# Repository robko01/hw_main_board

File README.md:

# hw_main_board
This repo is holding the Robko 01 main board design.

The board is designed in KiCAD.

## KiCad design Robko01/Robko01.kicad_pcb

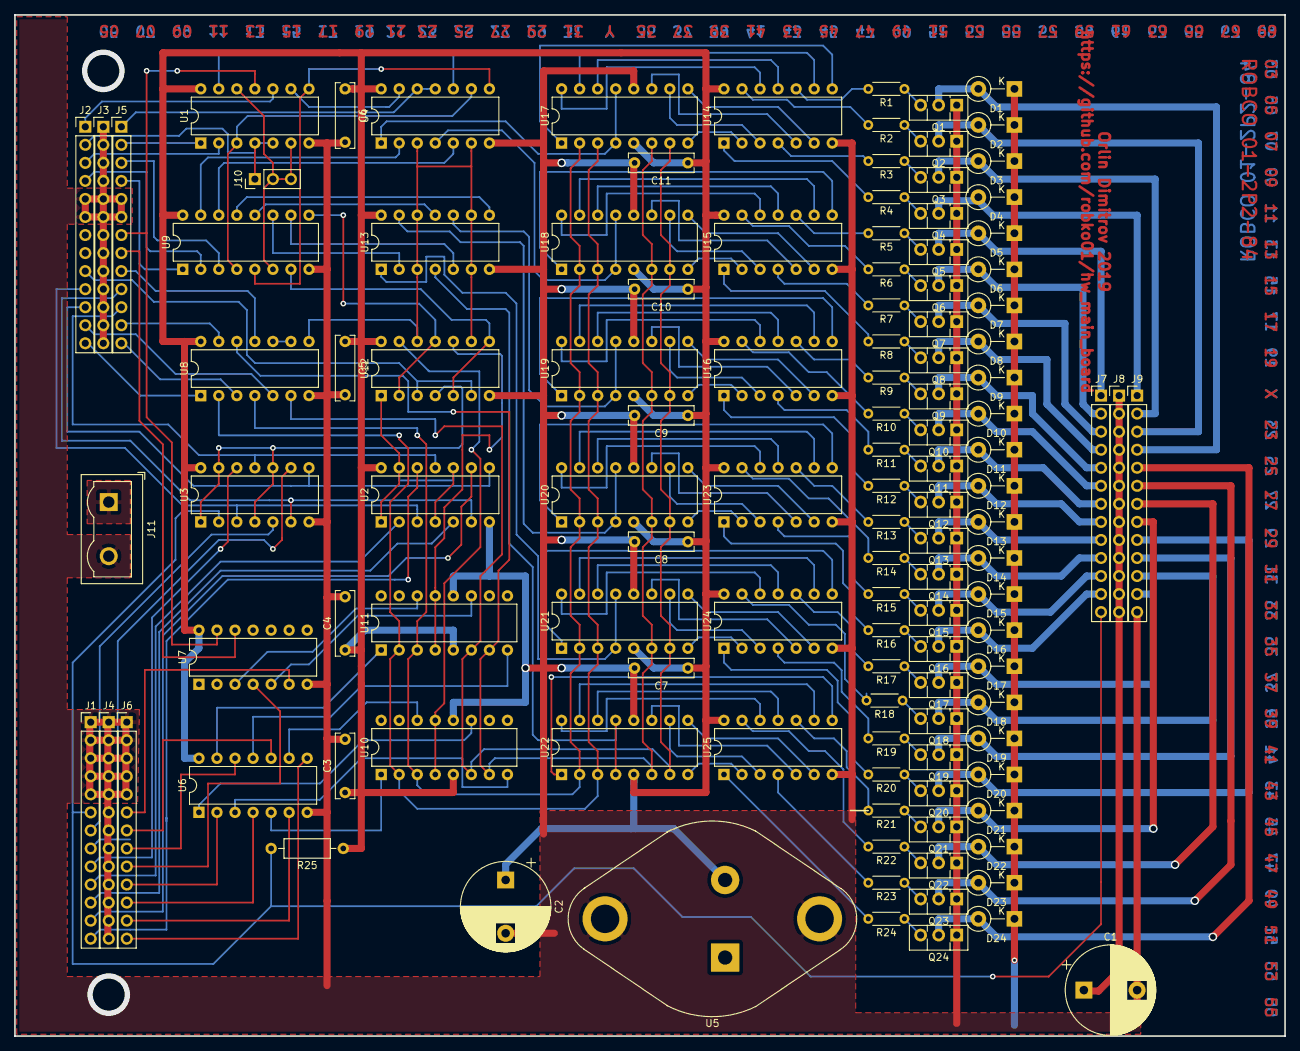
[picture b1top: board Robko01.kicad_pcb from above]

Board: 2 copper layers, 178.8 x 143.8 mm, 120 parts (0 on the bottom side), 196 nets.

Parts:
C1, C2: CP; CP_Radial_D12.5mm_P7.50mm
C3, C4, C5, C6, C7, C8, C9, C10, C11: 150nF; C_Rect_L9.0mm_W2.5mm_P7.50mm_MKT
D1, D2, D3, D4, D5, D6, D7, D8, D9, D10, D11, D12, D13, D14, D15, D16, D17, D18, D19, D20, D21, D22, D23, D24: 1N4007; D_DO-41_SOD81_P5.08mm_Vertical_KathodeUp
J1: AC; PinHeader_1x13_P2.54mm_Vertical
J2, J5: BA; PinHeader_1x13_P2.54mm_Vertical
J3: BB; PinHeader_1x13_P2.54mm_Vertical
J4: AB; PinHeader_1x13_P2.54mm_Vertical
J6: AA; PinHeader_1x13_P2.54mm_Vertical
J7, J8, J9: MA; PinHeader_1x13_P2.54mm_Vertical
J10: A_SEL; PinHeader_1x03_P2.54mm_Vertical
J11: Conn_01x02_Male; TerminalBlock_Wuerth_691311400102_P7.62mm
Q1, Q2, Q3, Q4, Q5, Q6, Q7, Q8, Q9, Q10, Q11, Q12, Q13, Q14, Q15, Q16, Q17, Q18, Q19, Q20, Q21, Q22, Q23, Q24: BD139; TO-126-3_Vertical
R1, R2, R3, R4, R5, R6, R7, R8, R9, R10, R11, R12, R13, R14, R15, R16, R17, R18, R19, R20, R21, R22, R23, R24: R; R_Axial_DIN0204_L3.6mm_D1.6mm_P5.08mm_Horizontal
R25: 10k; R_Axial_DIN0207_L6.3mm_D2.5mm_P10.16mm_Horizontal
U1: 7400; DIP-14_W7.62mm
U2, U3: 74126; DIP-14_W7.62mm
U4, U12, U13, U14, U15, U16, U23, U24, U25: 7402; DIP-14_W7.62mm
U5: L7805; TO-3
U6, U7: 7407; DIP-14_W7.62mm
U8: 74LS04; DIP-14_W7.62mm
U9: 74LS138; DIP-16_W7.62mm
U10, U11, U17, U18, U19, U20, U21, U22: 74LS75; DIP-16_W7.62mm

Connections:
+5V: C2.1, C3.1, C4.1, C5.1, C6.1, C7.1, C8.1, C9.1, C10.1, C11.1, R25.1, U1.14, U2.14, U3.14, U4.14, U5.2, U6.14, U7.14, U8.14, U9.16, U10.5, U11.5, U12.14, U13.14, U14.14, U15.14, U16.14, U17.5, U18.5, U19.5, U20.5, U21.5, U22.5, U23.14, U24.14, U25.14
+12V: C1.1, D1.1, D2.1, D3.1, D4.1, D5.1, D6.1, D7.1, D8.1, D9.1, D10.1, D11.1, D12.1, D13.1, D14.1, D15.1, D16.1, D17.1, D18.1, D19.1, D20.1, D21.1, D22.1, D23.1, D24.1, J8.1, J8.2, J8.3, J8.4, J8.5, J8.6, J8.7, J8.8, J8.9, J8.10, J8.11, J8.12, J8.13, J11.1, U5.1
A0: J5.4, U9.1
A1: J2.4, U9.2
A2: J5.3, U9.3
A3: J2.3, U1.2
A4: J5.2, U1.1
A5: J2.2, J10.1, U1.4, U1.5
A6: J5.1, U4.11, U4.12
A7: J2.1, U1.10
DI0: J5.13, U8.3
DI1: J2.13, U8.1
DI2: J5.12, U8.13
DI3: J2.12, U8.5
DO0: J5.11, U2.11, U3.11
DO1: J2.11, U2.8, U3.8
DO2: J5.10, U2.6, U3.6
DO3: J2.10, U2.3, U3.3
GND: C1.2, C2.2, C3.2, C4.2, C5.2, C6.2, C7.2, C8.2, C9.2, C10.2, C11.2, J1.1, J1.2, J1.3, J1.4, J1.5, J2.5, J2.6, J3.1, J3.2, J3.3, J3.4, J3.5, J3.6, J3.7, J3.8, J3.9, J3.10, J3.11, J3.12, J3.13, J4.1, J4.2, J4.3, J4.4, J4.5, J4.6, J4.7, J4.8, J4.9, J4.10, J4.11, J4.12, J4.13, J5.5, J5.6, J6.1, J6.2, J6.3, J6.4, J6.5, J9.13, J11.2, Q1.1, Q2.1, Q3.1, Q4.1, Q5.1, Q6.1, Q7.1, Q8.1, Q9.1, Q10.1, Q11.1, Q12.1, Q13.1, Q14.1, Q15.1, Q16.1, Q17.1, Q18.1, Q19.1, Q20.1, Q21.1, Q22.1, Q23.1, Q24.1, U1.7, U2.7, U3.7, U4.7, U5.3, U6.7, U7.7, U8.7, U9.8, U10.12, U11.12, U12.7, U13.7, U14.7, U15.7, U16.7, U17.12, U18.12, U19.12, U20.12, U21.12, U22.12, U23.7, U24.7, U25.7
GRIPPER: J1.6, J7.13, R25.2, U3.2
IOW: J5.9, U8.11
unnamed: D1.2, J9.4, Q1.2
unnamed: D2.2, J9.3, Q2.2
unnamed: D3.2, J9.2, Q3.2
unnamed: D4.2, J9.1, Q4.2
unnamed: D5.2, J7.1, Q5.2
unnamed: D6.2, J7.2, Q6.2
unnamed: D7.2, J7.3, Q7.2
unnamed: D8.2, J7.4, Q8.2
unnamed: D9.2, J7.5, Q9.2
unnamed: D10.2, J7.6, Q10.2
unnamed: D11.2, J7.7, Q11.2
unnamed: D12.2, J7.8, Q12.2
unnamed: D13.2, J7.9, Q13.2
unnamed: D14.2, J7.10, Q14.2
unnamed: D15.2, J7.11, Q15.2
unnamed: D16.2, J7.12, Q16.2
unnamed: D17.2, J9.12, Q17.2
unnamed: D18.2, J9.11, Q18.2
unnamed: D19.2, J9.10, Q19.2
unnamed: D20.2, J9.9, Q20.2
unnamed: D21.2, J9.8, Q21.2
unnamed: D22.2, J9.7, Q22.2
unnamed: D23.2, J9.6, Q23.2
unnamed: D24.2, J9.5, Q24.2
unnamed: J1.7, U3.5
unnamed: J1.8, U3.9
unnamed: J1.9, U3.12
unnamed: J1.10, U2.2
unnamed: J1.11, U2.5
unnamed: J1.12, U2.9
unnamed: J1.13, U2.12
unnamed: J6.6, U7.6
unnamed: J6.7, U6.10
unnamed: J6.8, U6.12
unnamed: J6.9, U7.4
unnamed: J6.10, U6.2
unnamed: J6.11, U6.4
unnamed: J6.12, U6.6
unnamed: J6.13, U6.8
unnamed: J10.2, J10.3, U1.6, U1.12, U9.6
unnamed: Q1.3, R1.1
unnamed: Q2.3, R2.1
unnamed: Q3.3, R3.1
unnamed: Q4.3, R4.1
unnamed: Q5.3, R5.1
unnamed: Q6.3, R6.1
unnamed: Q7.3, R7.1
unnamed: Q8.3, R8.1
unnamed: Q9.3, R9.1
unnamed: Q10.3, R10.1
unnamed: Q11.3, R11.1
unnamed: Q12.3, R12.1
unnamed: Q13.3, R13.1
unnamed: Q14.3, R14.1
unnamed: Q15.3, R15.1
unnamed: Q16.3, R16.1
unnamed: Q17.3, R17.1
unnamed: Q18.3, R18.1
unnamed: Q19.3, R19.1
unnamed: Q20.3, R20.1
unnamed: Q21.3, R21.1
unnamed: Q22.3, R22.1
unnamed: Q23.3, R23.1
unnamed: Q24.3, R24.1
unnamed: R1.2, U14.10
unnamed: R2.2, U14.13
unnamed: R3.2, U14.4
unnamed: R4.2, U14.1
unnamed: R5.2, U15.10
unnamed: R6.2, U15.13
unnamed: R7.2, U15.4
unnamed: R8.2, U15.1
unnamed: R9.2, U16.10
unnamed: R10.2, U16.13
unnamed: R11.2, U16.4
unnamed: R12.2, U16.1
unnamed: R13.2, U23.10
unnamed: R14.2, U23.13
unnamed: R15.2, U23.4
unnamed: R16.2, U23.1
unnamed: R17.2, U24.10
unnamed: R18.2, U24.13
unnamed: R19.2, U24.4
unnamed: R20.2, U24.1
unnamed: R21.2, U25.10
unnamed: R22.2, U25.13
unnamed: R23.2, U25.4
unnamed: R24.2, U25.1
unnamed: U1.3, U4.9, U9.4
unnamed: U1.8, U4.8, U9.5
unnamed: U1.9, U4.13
unnamed: U1.13, U4.10
unnamed: U4.2, U9.15
unnamed: U4.5, U9.14
unnamed: U8.9, U8.10
unnamed: U6.5, U10.1
unnamed: U8.2, U10.2, U11.2, U17.3, U18.3, U19.3, U20.3, U21.3, U22.3
unnamed: U8.4, U10.3, U11.3, U17.2, U18.2, U19.2, U20.2, U21.2, U22.2
unnamed: U8.6, U10.6, U11.6, U17.7, U18.7, U19.7, U20.7, U21.7, U22.7
unnamed: U8.12, U10.7, U11.7, U17.6, U18.6, U19.6, U20.6, U21.6, U22.6
unnamed: U6.3, U10.8
unnamed: U6.1, U10.11
unnamed: U10.4, U10.13, U12.13
unnamed: U6.9, U10.14
unnamed: U6.13, U11.1
unnamed: U6.11, U11.8
unnamed: U7.5, U11.11
unnamed: U11.4, U11.13, U12.10
unnamed: U7.3, U11.14
unnamed: U2.1, U2.4, U2.10, U2.13, U12.1
unnamed: U3.1, U3.4, U3.10, U3.13, U12.4
unnamed: U9.7, U12.5, U12.8
unnamed: U9.9, U12.2, U12.11
unnamed: U4.3, U4.6, U8.8, U12.9, U12.12, U13.3, U13.6, U13.9, U13.12
unnamed: U13.1, U21.4, U21.13
unnamed: U9.11, U13.2
unnamed: U13.4, U22.4, U22.13
unnamed: U9.10, U13.5
unnamed: U9.13, U13.8
unnamed: U13.10, U19.4, U19.13
unnamed: U9.12, U13.11
unnamed: U13.13, U20.4, U20.13
unnamed: U14.2, U17.8
unnamed: U14.3, U17.10
unnamed: U14.5, U17.11
unnamed: U14.6, U17.9
unnamed: U14.8, U17.1
unnamed: U14.9, U17.15
unnamed: U14.11, U17.14
unnamed: U14.12, U17.16
unnamed: U15.2, U18.8
unnamed: U15.3, U18.10
unnamed: U15.5, U18.11
unnamed: U15.6, U18.9
unnamed: U15.8, U18.1
unnamed: U15.9, U18.15
unnamed: U15.11, U18.14
unnamed: U15.12, U18.16
unnamed: U16.2, U19.8
unnamed: U16.3, U19.10
unnamed: U16.5, U19.11
unnamed: U16.6, U19.9
unnamed: U16.8, U19.1
unnamed: U16.9, U19.15
unnamed: U16.11, U19.14
unnamed: U16.12, U19.16
unnamed: U4.1, U17.4, U17.13
unnamed: U4.4, U18.4, U18.13
unnamed: U20.1, U23.8
unnamed: U20.8, U23.2
unnamed: U20.9, U23.6
unnamed: U20.10, U23.3
unnamed: U20.11, U23.5
unnamed: U20.14, U23.11
unnamed: U20.15, U23.9
unnamed: U20.16, U23.12
unnamed: U21.1, U24.8
unnamed: U21.8, U24.2
unnamed: U21.9, U24.6
unnamed: U21.10, U24.3
unnamed: U21.11, U24.5
unnamed: U21.14, U24.11
unnamed: U21.15, U24.9
unnamed: U21.16, U24.12
unnamed: U22.1, U25.8
unnamed: U22.8, U25.2
unnamed: U22.9, U25.6
unnamed: U22.10, U25.3
unnamed: U22.11, U25.5
unnamed: U22.14, U25.11
unnamed: U22.15, U25.9
unnamed: U22.16, U25.12
OE: J5.7, U1.11, U7.13
ÌOR: J2.9, U12.3, U12.6
ÒC-OE: J5.8, U7.12

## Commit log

2020-08-17 Add the board design
2020-08-17 Update READEME
2020-08-30 Add ignore file
